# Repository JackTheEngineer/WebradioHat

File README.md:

# WebradioHat
A Small Audio Hat for the Raspberry Pi Zero, with LCD Adapter and 6 GPIOs for Buttons. 
This Hat uses PWM for audio, and has no DAC. 
It currently has a small misalignment of the holes to the Raspberry.
I didn't do it carefully enough, any improvements are welcome.

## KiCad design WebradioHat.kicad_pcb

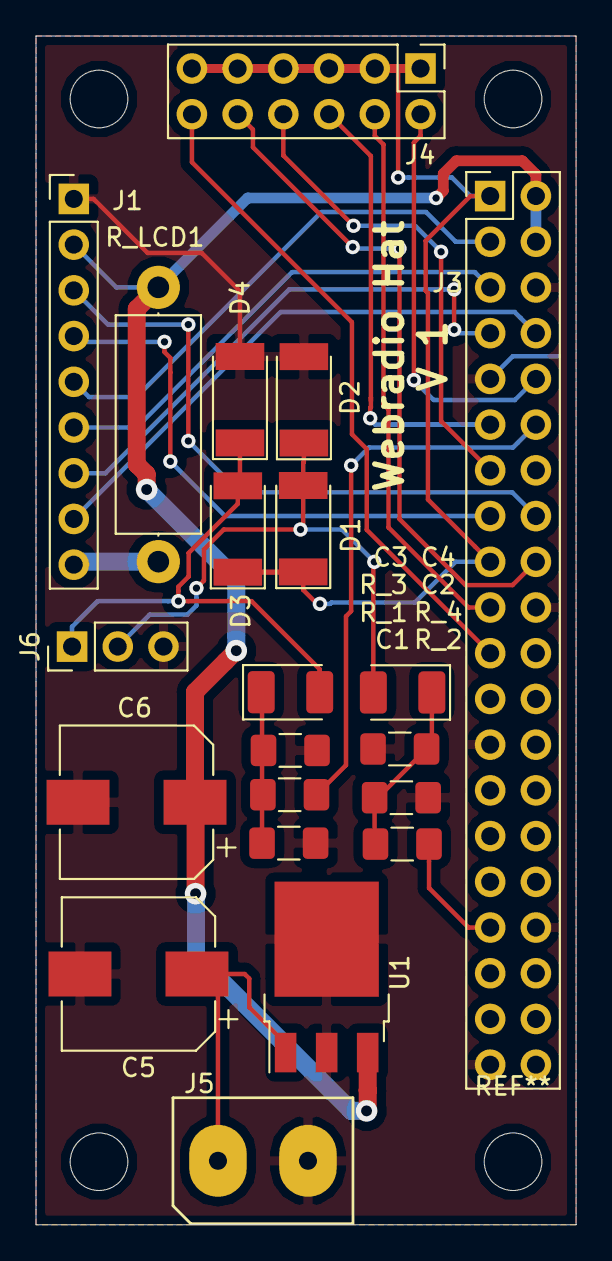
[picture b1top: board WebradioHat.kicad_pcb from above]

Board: 2 copper layers, 30.0 x 66.0 mm, 21 parts (0 on the bottom side), 23 nets.

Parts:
C1, C2: 33n; C_1206_3216Metric_Pad1.42x1.75mm_HandSolder
C3, C4: 10u; CP_EIA-3528-21_Kemet-B_Pad1.50x2.35mm_HandSolder
C5, C6: 47u; CP_Elec_8x10
D1, D2, D3, D4: D; D_MELF
J1: Female 9*1, LCD 4*16; PinHeader_1x09_P2.54mm_Vertical
J3: Conn_02x20_Odd_Even; PinHeader_2x20_P2.54mm_Vertical
J4: Conn_02x06_Odd_Even; PinHeader_2x06_P2.54mm_Vertical
J5: Screw_Terminal_01x02; Connector_XY306
J6: Sound L+R; PinHeader_1x03_P2.54mm_Vertical
R_1, R_2: 270 Ohm; R_1206_3216Metric_Pad1.42x1.75mm_HandSolder
R_3, R_4: 300 Ohm; R_1206_3216Metric_Pad1.42x1.75mm_HandSolder
R_LCD1: 22 Ohm; R_Axial_DIN0414_L11.9mm_D4.5mm_P15.24mm_Horizontal
U1: L7805; TO-252-3_TabPin2

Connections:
+3V3: D1.1, D3.1, J3.1, J3.17, J4.1, J4.3, J4.5, J4.7, J4.9, J4.11
+5V: C6.1, J1.2, J3.2, J3.4, R_LCD1.1, U1.3
CenterBTN: J3.10, J4.2
DownBTN: J3.21, J4.12
EnterBTN: J3.19, J4.4
GND: C1.2, C2.2, C5.2, C6.2, D2.2, D4.2, J1.1, J3.6, J3.9, J3.20, J3.25, J3.34, J3.39, J5.2, J6.3, R_3.2, R_4.2, U1.2
LCD_DB4: J1.5, J3.3
LCD_DB5: J1.6, J3.5
LCD_DB6: J1.7, J3.7
LCD_DB7: J1.8, J3.8
LCD_E: J1.4, J3.15
LCD_RS: J1.3, J3.16
LeftBTN: J3.11, J4.6
unnamed: C1.1, C3.1, R_1.2, R_3.1
unnamed: C2.1, C4.1, R_2.2, R_4.1
unnamed: C3.2, D3.2, D4.1, J6.1
unnamed: C4.2, D1.2, D2.1, J6.2
unnamed: C5.1, J5.1, U1.1
unnamed: J1.9, R_LCD1.2
RightBTN: J3.13, J4.8
SND_L: J3.12, R_1.1
SND_R: J3.33, R_2.1
UpBTN: J3.18, J4.10

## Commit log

2018-11-18 save commit before destroyed hat completely
2018-11-18 chng README
